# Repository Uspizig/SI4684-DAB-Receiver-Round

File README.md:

# Note:
The version in the repository is an ongoing development. It could and will contain bugs. To make sure you use the latest fully tested firmware, check the releases!

# Hint:
#define USE_HSPI_PORT ... set this to active in eTFT Lib user_setup.h. otherwise it won't work

# SI4684 DAB receiver
Advanced DAB Tuner software for Skyworks SI4684 tuner with ESP32 board and a round color LCD or AMOLED\
This is a fork of the famous PE5PVB SI4684 Project, unfinished and right now still in devolpment.
Check a more developed project on the origin source: https://www.pe5pvb.nl/

# How does it look

Simulation

Real device

# How does it look working

These are pictures of the very first HW bringup

Base Screen:

DAB Slideshow

# Libraries
These are the libraries used for this project:
- https://github.com/Bodmer/TFT_eSPI
- https://github.com/uzi18/TFT_eSPI
- https://github.com/Bodmer/JPEGDecoder
- https://github.com/bitbank2/PNGdec

Use these settings in the TFT_eSPI library:
```
#define ILI9341_2_DRIVER     // Alternative ILI9341 driver, see https://github.com/Bodmer/TFT_eSPI/issues/1172
#define TFT_WIDTH  240 // ST7789 240 x 240 and 240 x 320
#define TFT_HEIGHT 320 // ST7789 240 x 320

#define TFT_CS    38  // Chip select PIN
#define TFT_MISO  39  // MISO PIN
#define TFT_DC    40  // Data Command control pin
#define TFT_RST   41  // Reset pin (could connect 
#define TFT_MOSI  42  // MOSI PIN
#define TFT_SCLK  10  // CLK PIN
#define SPI_FREQUENCY  27000000
#define SMOOTH_FONT
#define USE_HSPI_PORT ///// THIS IS IMPORTANT OTHERWISE NO CONTACT TO DAB TUNER
#define LOAD_GFXFF  // FreeFonts. Include access to the 48 Adafruit_GFX free fonts FF1 to FF48 and custom fonts
#define SPI_READ_FREQUENCY  20000000
#define SPI_TOUCH_FREQUENCY  2500000

```
# Buttons
A brief instruction for the buttons:
- Top encoder: Choose frequency or memory channel
- Bottom encoder: Choose service or set headphones volume
- (Not in use right now) Top button: Short press: Service information, Long press: Stand-by mode. 
- Middle button: Short press: Set mode, Long press: Open menu.
- Lower button: Toggle Slideshow view.
  
## Contributing
I'm open for a new ideas in our project. Feel free to share your thoughts in 

You are using my software and you found a difficulty? Please create new [issue] and describe your problem.

I also would like to invite you to join our Discord community where we share our ideas and help each other with some issues.\

Special thanks to all [contributors](https://github.com/PE5PVB/TEF-Nextion-Multiband/graphs/contributors). You are awesome! ❤️
## License
This program is free software; you can redistribute it and/or modify it under the terms of the GNU General Public License as published by the Free Software Foundation; either version 3 of the License, or (at your option) any later version.

This program is distributed in the hope that it will be useful, but WITHOUT ANY WARRANTY; without even the implied warranty of MERCHANTABILITY or FITNESS FOR A PARTICULAR PURPOSE. See the GNU General Public License for more details. 

## If you like this software. Contriubute to

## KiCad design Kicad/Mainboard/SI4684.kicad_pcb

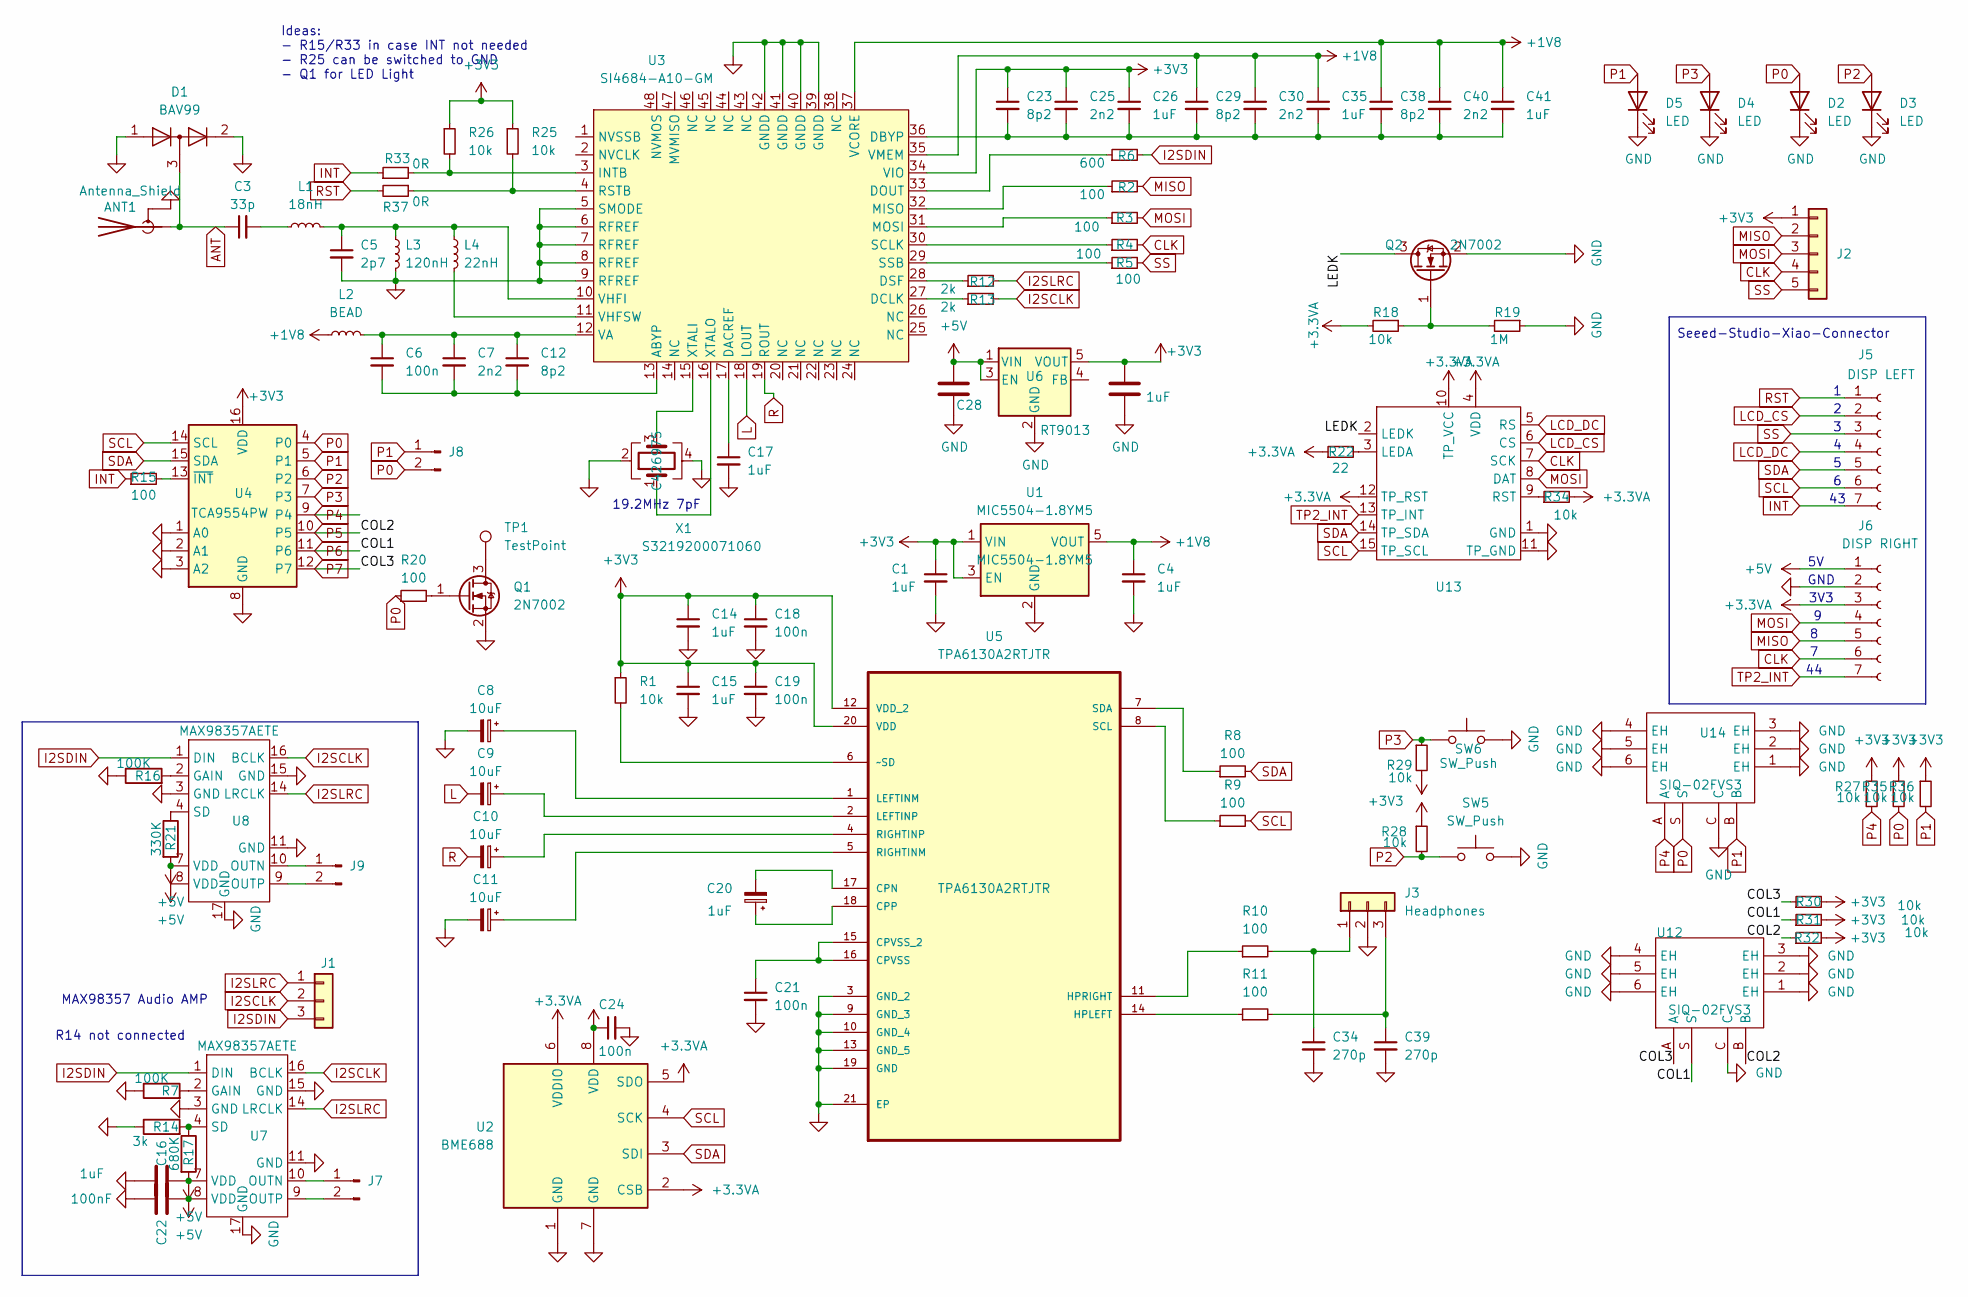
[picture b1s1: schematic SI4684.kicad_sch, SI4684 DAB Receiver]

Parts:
ANT1: Antenna_Shield; SMA_Samtec_SMA-J-P-H-ST-EM1_EdgeMount
C1, C4, C14, C15, C16, C17, C20, C26, C35, C41: 1uF; C_0603_1608Metric
C3: 33p; C_0603_1608Metric
C5: 2p7; C_0603_1608Metric_Pad1.08x0.95mm_HandSolder
C6, C18, C19, C21, C24: 100n; C_0603_1608Metric
C7, C25, C30, C40: 2n2; C_0603_1608Metric
C8, C9, C10, C11: 10uF; C_0805_2012Metric_Pad1.18x1.45mm_HandSolder
C12, C23, C29, C38: 8p2; C_0603_1608Metric
C22: 100nF; C_0603_1608Metric_Pad1.08x0.95mm_HandSolder
C28, C31: 1uF; C_0805_2012Metric_Pad1.18x1.45mm_HandSolder
C34, C39: 270p; C_0603_1608Metric
D1: BAV99; SOT-23W
D2, D4, D5: LED; LED_1210_3225Metric_Pad1.42x2.65mm_HandSolder
D3: LED; LED_1210_3225Metric
J1: Conn_01x03; PinHeader_1x03_P2.54mm_Vertical
J2: Conn_01x05; PinSocket_1x05_P2.54mm_Vertical_SMD_Pin1Left
J3: Headphones; JST_PH_B3B-PH-K_1x03_P2.00mm_Vertical
J5: DISP LEFT; PinHeader_1x07_P2.54mm_Vertical
J6: DISP RIGHT; PinHeader_1x07_P2.54mm_Vertical
J7, J9: Conn_01x02_Pin; PinHeader_1x02_P2.00mm_Vertical
J8: Conn_01x02_Pin; PinHeader_1x02_P2.54mm_Vertical
L1: 18nH; L_0603_1608Metric_Pad1.05x0.95mm_HandSolder
L2: BEAD; L_0603_1608Metric
L3: 120nH; L_0603_1608Metric_Pad1.05x0.95mm_HandSolder
L4: 22nH; L_0603_1608Metric_Pad1.05x0.95mm_HandSolder
Q1, Q2: 2N7002; SOT-23
R1, R18, R25, R26: 10k; R_0603_1608Metric
R2, R3, R4, R5, R8, R9, R10, R11, R15, R20: 100; R_0603_1608Metric
R6: 600; R_0603_1608Metric
R7, R16: 100K; R_0603_1608Metric_Pad0.98x0.95mm_HandSolder
R12, R13: 2k; R_0603_1608Metric
R14: 3k; R_0603_1608Metric_Pad0.98x0.95mm_HandSolder
R17: 680K; R_0603_1608Metric_Pad0.98x0.95mm_HandSolder
R19: 1M; R_0603_1608Metric
R21: 330K; R_0603_1608Metric_Pad0.98x0.95mm_HandSolder
R22: 22; R_0603_1608Metric
R27, R28, R29, R35, R36: 10k; R_0805_2012Metric_Pad1.20x1.40mm_HandSolder
R30, R31, R32, R34: 10k; R_0603_1608Metric_Pad0.98x0.95mm_HandSolder
R33, R37: 0R; R_0603_1608Metric
SW5, SW6: SW_Push; SW_SPST_CK_KMS2xxGP
TP1: TestPoint; TestPoint_Pad_D1.0mm
U1: MIC5504-1.8YM5; SOT-23-5
U2: BME688; Bosch_LGA-8_3x3mm_P0.8mm_ClockwisePinNumbering
U3: SI4684-A10-GM; QFN-48-1EP_7x7mm_P0.5mm_EP5.3x5.3mm
U4: TCA9554PW; TSSOP-16_4.4x5mm_P0.65mm
U5: TPA6130A2RTJTR; QFN-20-1EP_4x4mm_P0.5mm_EP2.7x2.7mm; MPN TPA6130A2RTJTR
U6: RT9013; SOT-23-5
U7, U8: MAX98357AETE; TQFN-16_L3.0-W3.0-P0.50-BL-EP1.5
U12, U14: SIQ-02FVS3; SW-SMD_SIQ-02FVS3_1; Manufacturer Part SIQ-02FVS3; LCSC Part Name 拨轮滚轮旋转编码器开关
U13: GC9A01_Touch_IPS_display_reversed_16pin
X1: S3219200071060; Crystal_SMD_3225-4Pin_3.2x2.5mm

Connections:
+1V8: C4.1, C29.1, C30.1, C35.1, C38.1, C40.1, C41.1, L2.1, U1.5 (VOUT), U3.35 (VMEM), U3.37 (VCORE)
+3.3VA: C24.1, J6.3, R18.2, R22.1, R34.2, U2.2 (CSB), U2.5 (SDO), U2.6 (VDDIO), U2.8 (VDD), U13.4 (VDD), U13.10 (TP_VCC), U13.12 (TP_RST)
+3V3: C1.1, C14.1, C15.1, C18.1, C19.1, C23.1, C25.1, C26.1, C31.2, J2.1, R1.1, R25.1, R26.1, R27.1, R28.1, R29.2, R30.2, R31.2, R32.2, R35.1, R36.1, U1.1 (VIN), U1.3 (EN), U3.34 (VIO), U4.16 (VDD), U5.12 (VDD_2), U5.20 (VDD), U6.5 (VOUT)
+5V: C16.1, C22.1, C28.2, J6.1, R17.2, R21.2, U6.1 (VIN), U6.3 (EN), U7.7 (VDD), U7.8 (VDD), U8.7 (VDD), U8.8 (VDD)
/LEDK: Q2.3 (D), U13.2 (LEDK)
ANT: ANT1.1 (A), C3.1, D1.3 (K); also elsewhere on the board
CLK: J2.4, J6.6, R4.2, U13.7 (SCK)
GND: ANT1.2 (Shield), C1.2, C4.2, C5.2, C8.2, C11.2, C14.2, C15.2, C16.2, C17.2, C18.2, C19.2, C21.2, C22.2, C24.2, C28.1, C31.1, C34.2, C39.2, D1.1 (K), D1.2 (A), D2.1 (K), D3.1 (K), D4.1 (K), D5.1 (K), J3.2, J6.2, L3.2, Q1.2 (S), Q2.2 (S), R7.1, R14.1, R16.1, R19.1, SW5.2, SW6.2, U1.2 (GND), U2.1 (GND), U2.7 (GND), U3.5 (SMODE), U3.6 (RFREF), U3.7 (RFREF), U3.8 (RFREF), U3.9 (RFREF), U3.39 (GNDD), U3.40 (GNDD), U3.41 (GNDD), U3.42 (GNDD), U3.49 (GND), U4.1 (A0), U4.2 (A1), U4.3 (A2), U4.8 (GND), U5.3 (GND_2), U5.9 (GND_3), U5.10 (GND_4), U5.13 (GND_5), U5.19 (GND), U5.21 (EP), U6.2 (GND), U7.3 (GND), U7.11 (GND), U7.15 (GND), U7.17 (GND), U8.3 (GND), U8.11 (GND), U8.15 (GND), U8.17 (GND), U12.1 (EH), U12.2 (EH), U12.3 (EH), U12.4 (EH), U12.5 (EH), U12.6 (EH), U12.C, U13.1 (GND), U13.11 (TP_GND), U14.1 (EH), U14.2 (EH), U14.3 (EH), U14.4 (EH), U14.5 (EH), U14.6 (EH), U14.C, X1.2, X1.4; also elsewhere on the board
I2SCLK: J1.2, R13.2, U7.16 (BCLK), U8.16 (BCLK)
I2SDIN: J1.3, R6.2, U7.1 (DIN), U8.1 (DIN)
I2SLRC: J1.1, R12.2, U7.14 (LRCLK), U8.14 (LRCLK)
INT: J5.7, R15.1, R33.1
L: C9.2, U3.18 (LOUT)
LCD_CS: J5.2, U13.6 (CS)
LCD_DC: J5.4, U13.5 (RS)
MISO: J2.2, J6.5, R2.2
MOSI: J2.3, J6.4, R3.2, U13.8 (DAT)
unnamed: C3.2, L1.1
unnamed: C34.1, J3.1, R10.2
unnamed: C39.1, J3.3, R11.2
unnamed: J7.1, U7.10 (OUTN)
unnamed: J7.2, U7.9 (OUTP)
unnamed: J9.1, U8.10 (OUTN)
unnamed: J9.2, U8.9 (OUTP)
unnamed: Q1.3 (D), TP1.1
unnamed: Q1.1 (G), R20.2
unnamed: Q2.1 (G), R18.1, R19.2
unnamed: C6.2, C7.2, C12.2, U3.13 (ABYP)
unnamed: C17.1, U3.17 (DACREF)
unnamed: C23.2, C25.2, C26.2, C29.2, C30.2, C35.2, C38.2, C40.2, C41.2, U3.36 (DBYP)
unnamed: R13.1, U3.27 (DCLK)
unnamed: R6.1, U3.33 (DOUT)
unnamed: R12.1, U3.28 (DSF)
unnamed: R26.2, R33.2, U3.3 (INTB)
unnamed: R2.1, U3.32 (MISO)
unnamed: R3.1, U3.31 (MOSI)
unnamed: R25.2, R37.1, U3.4 (RSTB)
unnamed: R4.1, U3.30 (SCLK)
unnamed: R5.1, U3.29 (SSB)
unnamed: C6.1, C7.1, C12.1, L2.2, U3.12 (VA)
unnamed: C5.1, L1.2, L3.1, L4.1, U3.10 (VHFI)
unnamed: L4.2, U3.11 (VHFSW)
unnamed: U3.15 (XTALI), X1.3
unnamed: U3.16 (XTALO), X1.1
unnamed: R15.2, U4.13 (~INT)
unnamed: C20.2, U5.17 (CPN)
unnamed: C20.1, U5.18 (CPP)
unnamed: C21.1, U5.15 (CPVSS_2), U5.16 (CPVSS)
unnamed: R11.1, U5.14 (HPLEFT)
unnamed: R10.1, U5.11 (HPRIGHT)
unnamed: C8.1, U5.1 (LEFTINM)
unnamed: C9.1, U5.2 (LEFTINP)
unnamed: C11.1, U5.5 (RIGHTINM)
unnamed: C10.1, U5.4 (RIGHTINP)
unnamed: R9.1, U5.8 (SCL)
unnamed: R8.1, U5.7 (SDA)
unnamed: R1.2, U5.6 (~SD)
unnamed: R7.2, U7.2 (GAIN)
unnamed: R14.2, R17.1, U7.4 (SD)
unnamed: R16.2, U8.2 (GAIN)
unnamed: R21.1, U8.4 (SD)
unnamed: R22.2, U13.3 (LEDA)
unnamed: R34.1, U13.9 (RST)
P0: D2.2 (A), J8.2, R20.1, R35.2, U4.4 (P0), U14.S
P1: D5.2 (A), J8.1, R36.2, U4.5 (P1), U14.B
P2: D3.2 (A), R28.2, SW5.1, U4.6 (P2)
P3: D4.2 (A), R29.1, SW6.1, U4.7 (P3)
P4: R27.2, U4.9 (P4), U14.A
P5: R32.1, U4.10 (P5), U12.B
P6: R31.1, U4.11 (P6), U12.S
P7: R30.1, U4.12 (P7), U12.A
R: C10.2, U3.19 (ROUT)
RST: J5.1, R37.2
SCL: J5.6, R9.2, U2.4 (SCK), U4.14 (SCL), U13.15 (TP_SCL)
SDA: J5.5, R8.2, U2.3 (SDI), U4.15 (SDA), U13.14 (TP_SDA)
SS: J2.5, J5.3, R5.2
TP2_INT: J6.7, U13.13 (TP_INT)

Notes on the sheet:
R14 not connected
MAX98357 Audio AMP
3V3
Seeed-Studio-Xiao-Connector
Ideas: - R15/R33 in case INT not needed - R25 can be switched to GND - Q1 for LED Light
19.2MHz 7pF
GND

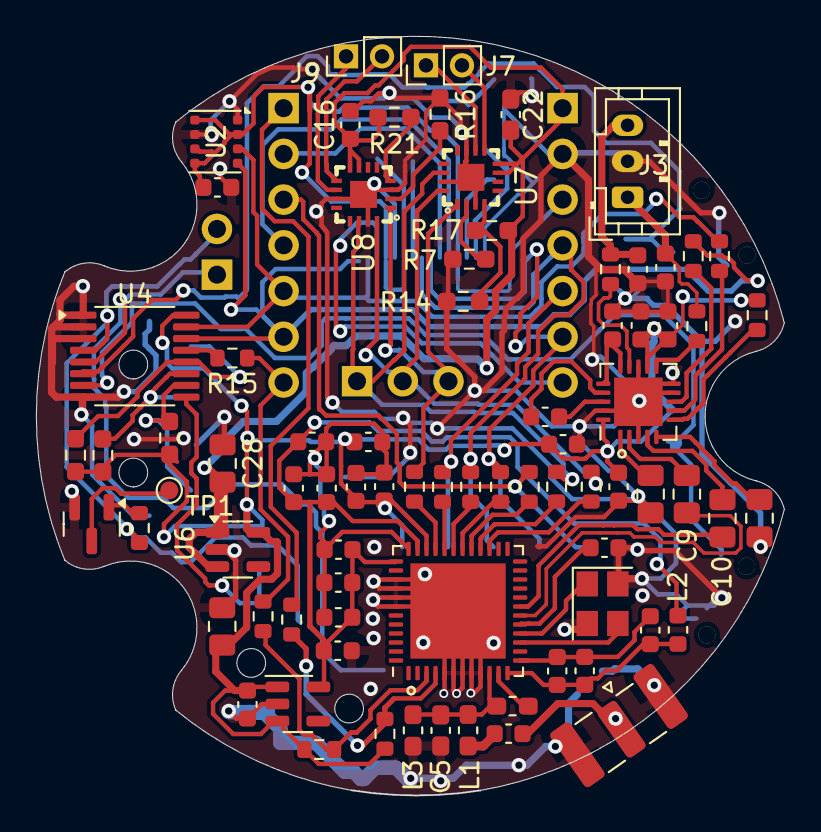
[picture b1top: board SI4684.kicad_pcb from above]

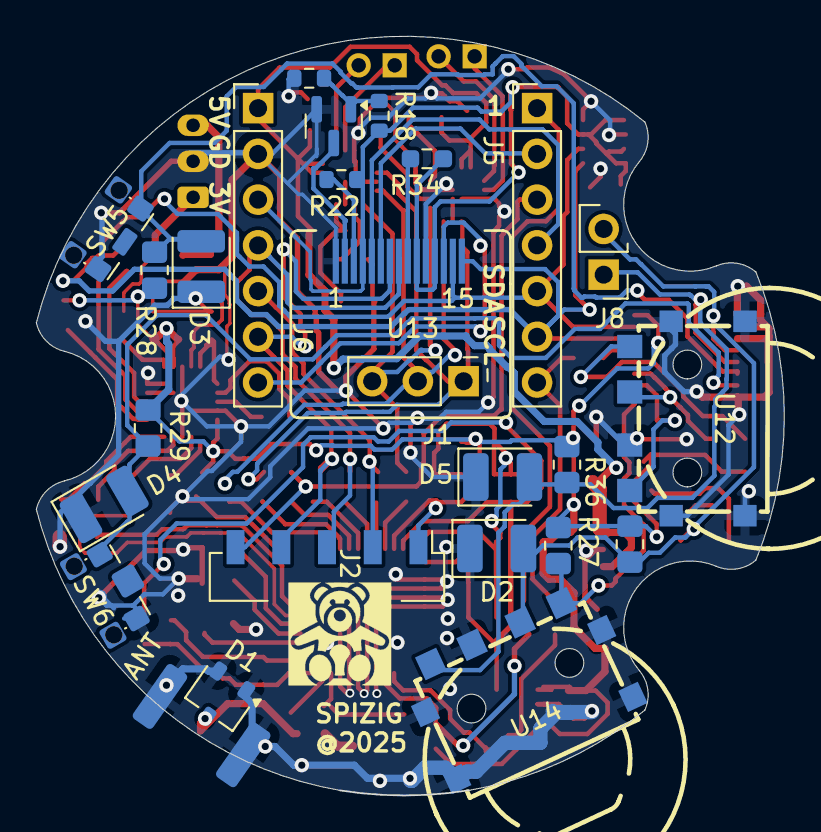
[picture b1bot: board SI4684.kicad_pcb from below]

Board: 2 copper layers, 41.6 x 42.2 mm, 105 parts (26 on the bottom side), 77 nets.

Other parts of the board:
ANT: Antenna_Shield; SMA_Samtec_SMA-J-P-H-ST-EM1_EdgeMount
H2: MountingHole; baerklein

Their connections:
ANT: ANT.1 (A); also elsewhere on the board
GND: ANT.2 (Shield); also elsewhere on the board

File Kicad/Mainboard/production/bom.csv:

Designator,Footprint,Quantity,Value,LCSC Part #
ANT,SMA_Samtec_SMA-J-P-H-ST-EM1_EdgeMount,1,Antenna_Shield,
"C1, C14, C15, C16, C17, C20, C26, C35, C4, C41",0603,10,1uF,
"C10, C11, C8, C9",0805,4,10uF,
"C12, C23, C29, C38",0603,4,8p2,
"C18, C19, C21, C24, C6",0603,5,100n,
C22,0603,1,100nF,
"C25, C30, C40, C7",0603,4,2n2,
"C28, C31",0805,2,1uF,
C3,0603,1,33p,
"C34, C39",0603,2,270p,
C5,0603,1,2p7,
D1,SOT-23W,1,BAV99,
"D2, D3, D4, D5",1210,4,LED,
J1,PinHeader_1x03_P2.54mm_Vertical,1,Conn_01x03,
J2,PinSocket_1x05_P2.54mm_Vertical_SMD_Pin1Left,1,Conn_01x05,
J3,JST_PH_B3B-PH-K_1x03_P2.00mm_Vertical,1,Headphones,
J5,PinHeader_1x07_P2.54mm_Vertical,1,DISP LEFT,
J6,PinHeader_1x07_P2.54mm_Vertical,1,DISP RIGHT,
"J7, J9",PinHeader_1x02_P2.00mm_Vertical,2,Conn_01x02_Pin,
J8,PinHeader_1x02_P2.54mm_Vertical,1,Conn_01x02_Pin,
L1,0603,1,18nH,
L2,0603,1,BEAD,
L3,0603,1,120nH,
L4,0603,1,22nH,
"Q1, Q2",SOT-23,2,2N7002,
"R1, R18, R25, R26, R30, R31, R32, R34",0603,8,10k,
"R10, R11, R15, R2, R20, R3, R4, R5, R8, R9",0603,10,100,
"R12, R13",0603,2,2k,
R14,0603,1,3k,
"R16, R7",0603,2,100K,
R17,0603,1,680K,
R19,0603,1,1M,
R21,0603,1,330K,
R22,0603,1,22,
"R27, R28, R29, R35, R36",0805,5,10k,
"R33, R37",0603,2,0R,
R6,0603,1,600,
"SW5, SW6",SW_SPST_CK_KMS2xxGP,2,SW_Push,
TP1,TestPoint_Pad_D1.0mm,1,TestPoint,
U1,SOT-23-5,1,MIC5504-1.8YM5,
"U12, U14",SW-SMD_SIQ-02FVS3_1,2,SIQ-02FVS3,
U13,GC9A01_Touch_IPS_display_reversed_16pin,1,~,
U2,Bosch_LGA-8_3x3mm_P0.8mm_ClockwisePinNumbering,1,BME688,
U3,QFN-48-1EP_7x7mm_P0.5mm_EP5.3x5.3mm,1,SI4684-A10-GM,
U4,TSSOP-16_4.4x5mm_P0.65mm,1,TCA9554PW,
U5,QFN-20-1EP_4x4mm_P0.5mm_EP2.7x2.7mm,1,TPA6130A2RTJTR,  TPA6130A2RTJTR
U6,SOT-23-5,1,RT9013,
"U7, U8",TQFN-16_L3.0-W3.0-P0.50-BL-EP1.5,2,MAX98357AETE,
X1,Crystal_SMD_3225-4Pin_3.2x2.5mm,1,S3219200071060,

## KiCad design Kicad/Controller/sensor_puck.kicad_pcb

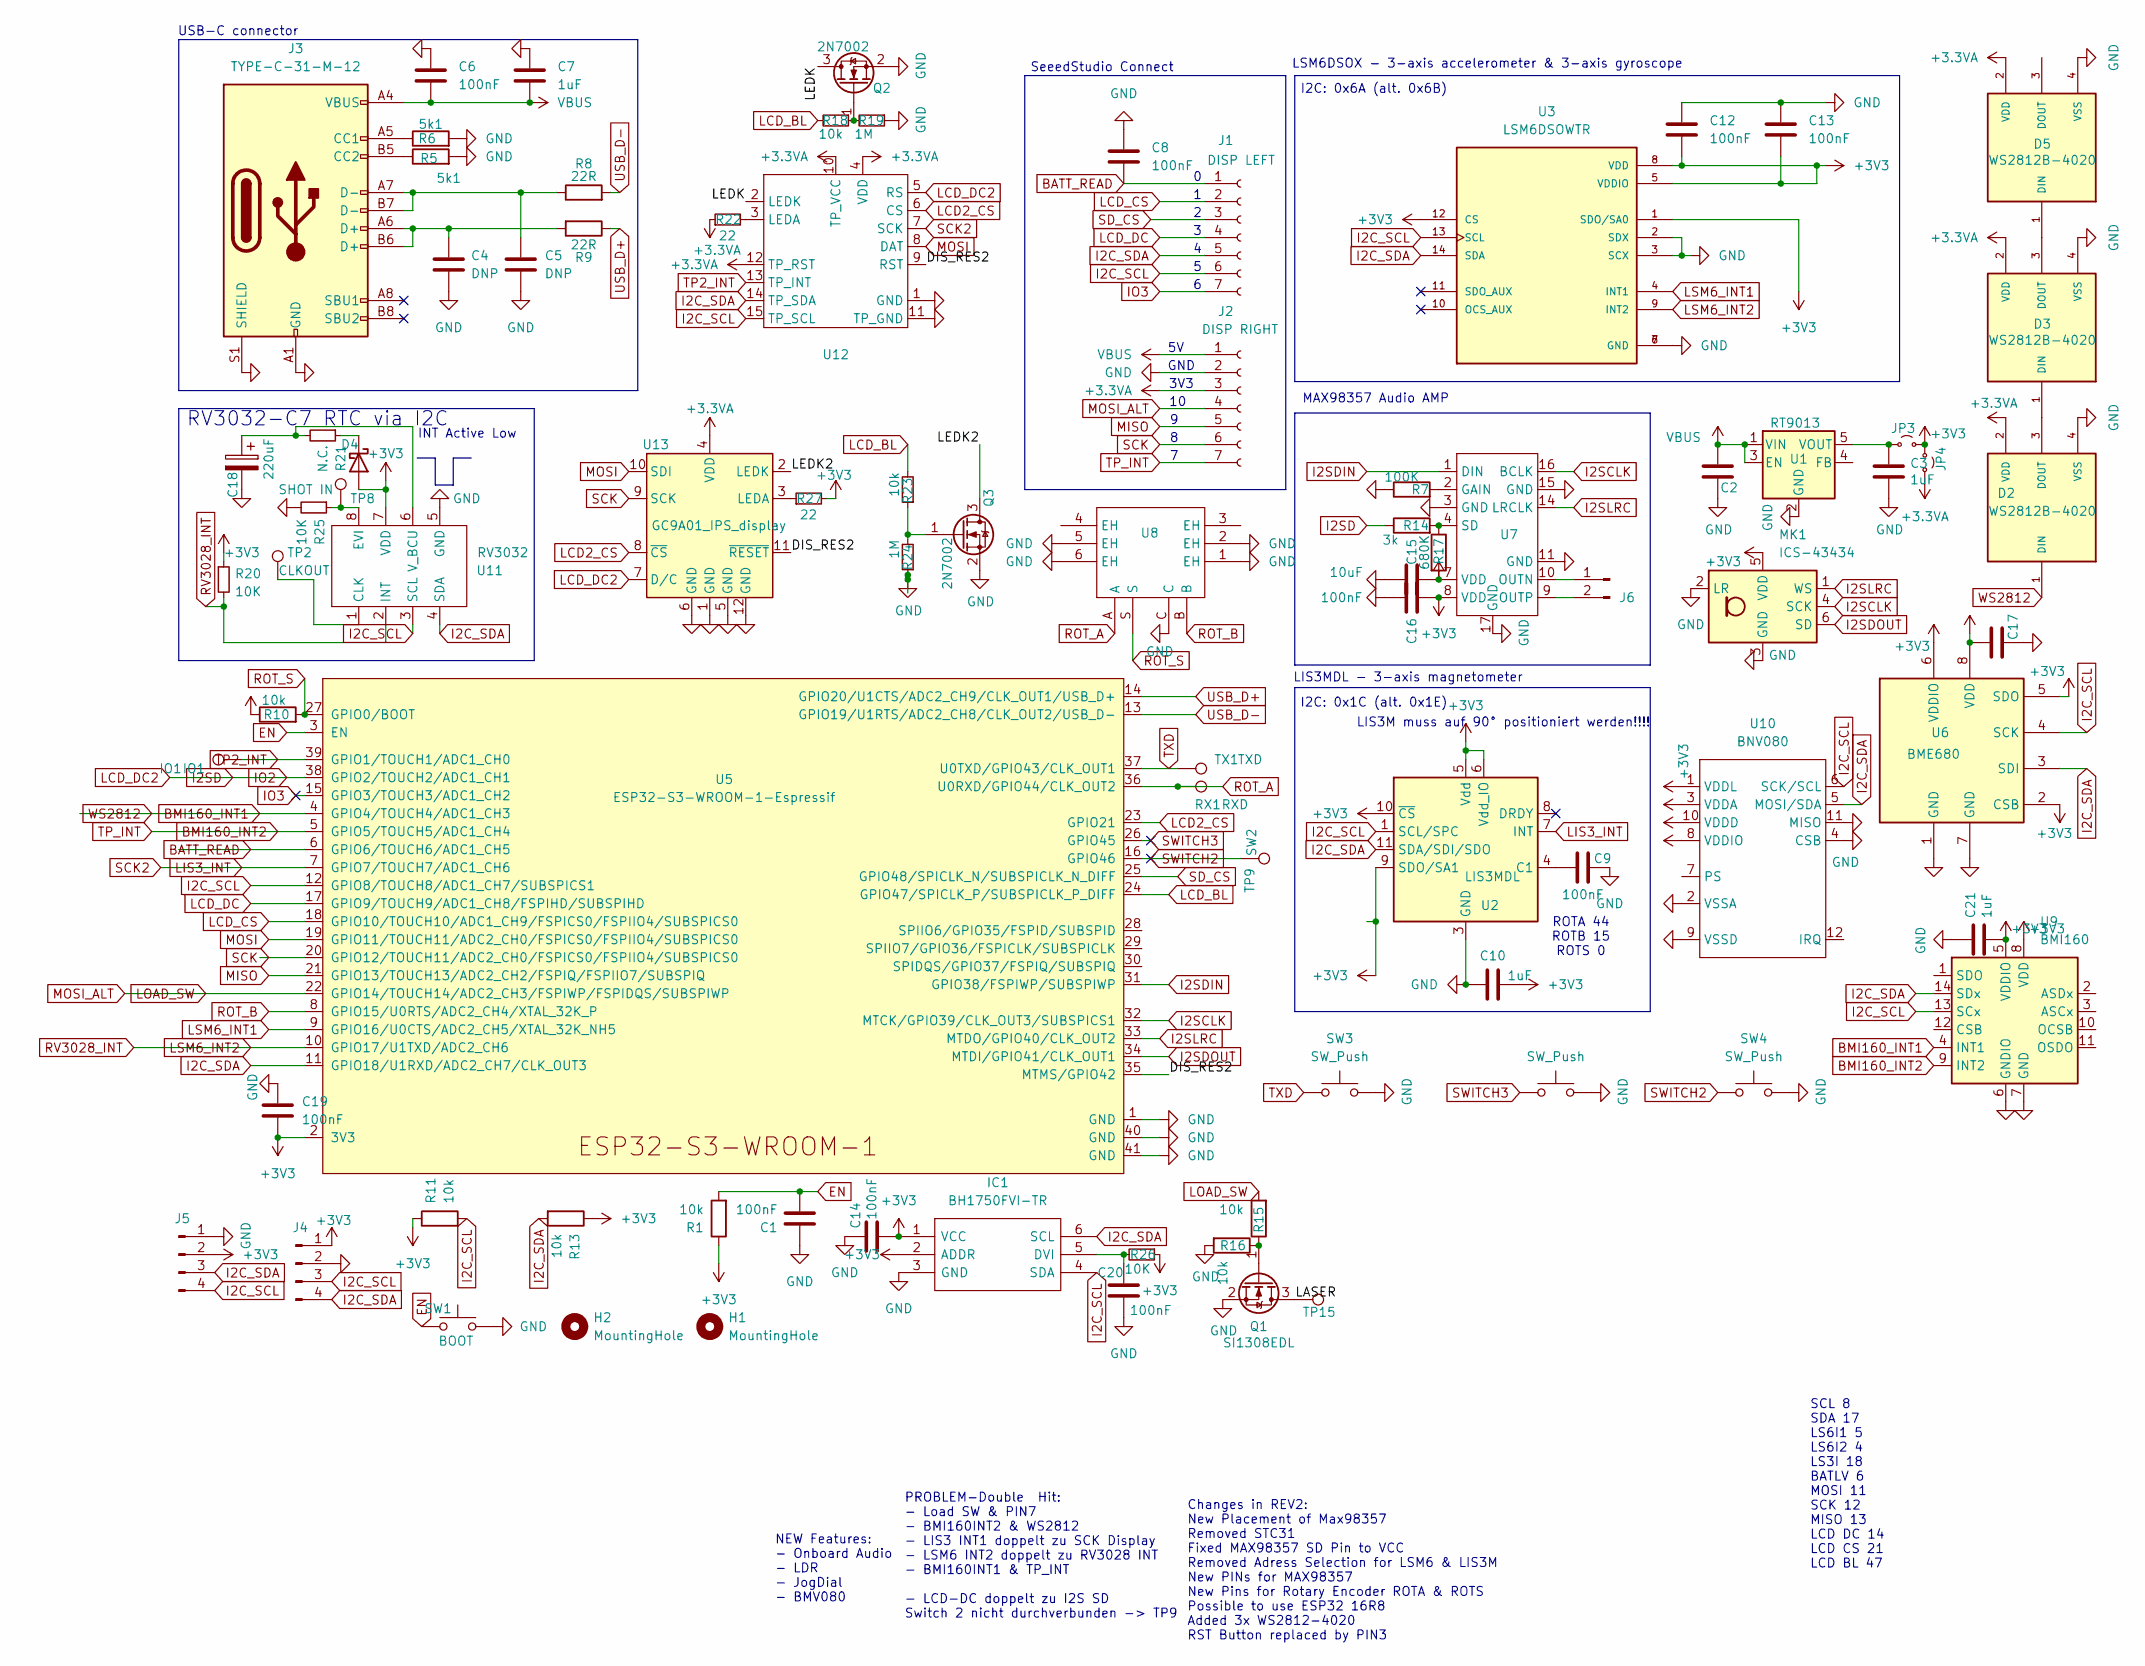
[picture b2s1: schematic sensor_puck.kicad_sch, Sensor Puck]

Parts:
C1: 100nF; C_1206_3216Metric_Pad1.33x1.80mm_HandSolder
C2, C3, C17, C21: 1uF; C_0805_2012Metric_Pad1.18x1.45mm_HandSolder
C4, C5: DNP; C_0805_2012Metric
C6, C8, C9, C12, C13, C14, C19: 100nF; C_0805_2012Metric
C7, C10: 1uF; C_0805_2012Metric
C15: 10uF; C_0805_2012Metric_Pad1.18x1.45mm_HandSolder
C16: 100nF; C_0805_2012Metric_Pad1.18x1.45mm_HandSolder
C18: 220uF; CP_EIA-3528-21_Kemet-B
C20: 100nF; C_0603_1608Metric
D2, D3, D5: WS2812B-4020; LED_WS2812B-4020; PARTREV V1.2
D4: MBR0530; D_SOD-323F
H1, H2: MountingHole; baerklein
IC1: BH1750FVI-TR; WSOF6; Mouser Part Number 755-BH1750FVI-TR
IO1: IO1; TestPoint_Pad_1.0x1.0mm
J1: DISP LEFT; PinHeader_1x07_P2.54mm_Vertical
J2: DISP RIGHT; PinHeader_1x07_P2.54mm_Vertical
J3: TYPE-C-31-M-12; USB-C_SMD-TYPE-C-31-M-12
J4: Conn_01x04_Pin; PinHeader_1x04_P2.54mm_Vertical_SMD_Pin1Left
J5: Conn_01x04_Pin; JST_SH_SM04B-SRSS-TB_1x04-1MP_P1.00mm_Horizontal
J6: Conn_01x02_Pin; PinHeader_1x02_P2.00mm_Vertical
JP3, JP4: Jumper_2_Small_Open; SolderJumper-2_P1.3mm_Open_RoundedPad1.0x1.5mm
MK1: ICS-43434; InvenSense_ICS-43434-6_3.5x2.65mm
Q1: SI1308EDL; SOT-323_SC-70
Q2, Q3: 2N7002; SOT-23
R1: 10k; R_0805_2012Metric_Pad1.20x1.40mm_HandSolder
R5, R6: 5k1; R_0805_2012Metric
R7: 100K; R_0805_2012Metric_Pad1.20x1.40mm_HandSolder
R8, R9: 22R; R_0805_2012Metric
R10, R11, R13: 10k; R_0805_2012Metric
R14: 3k; R_0805_2012Metric_Pad1.20x1.40mm_HandSolder
R15, R16: 10k; R_0603_1608Metric_Pad0.98x0.95mm_HandSolder
R17: 680K; R_0805_2012Metric_Pad1.20x1.40mm_HandSolder
R18, R23: 10k; R_0603_1608Metric
R19, R24: 1M; R_0603_1608Metric
R20, R25, R26: 10K; R_0603_1608Metric_Pad0.98x0.95mm_HandSolder; LCSC C17414
R21: N.C.; C_0603_1608Metric
R22, R27: 22; R_0603_1608Metric
RX1: RXD; TestPoint_Pad_1.0x1.0mm
SW1: BOOT; SW_PUSH_6mm
SW3, SW4, SW6: SW_Push; SW_SPST_CK_KMS2xxGP
TP2: CLKOUT; TestPoint_Pad_D1.0mm
TP8: SHOT IN; TestPoint_Pad_D1.0mm
TP9: SW2; TestPoint_Pad_D1.0mm
TP15: TestPoint; TestPoint_Pad_D1.0mm
TX1: TXD; TestPoint_Pad_1.0x1.0mm
U1: RT9013; SOT-23-5
U2: LIS3MDL; LGA-12_2x2mm_P0.5mm
U3: LSM6DSOWTR; LGA-14_3x2.5mm_P0.5mm_LayoutBorder3x4y; PARTREV 3.0
U5: ESP32-S3-WROOM-1-Espressif; ESP32-S3-WROOM-1
U6: BME680; Bosch_LGA-8_3x3mm_P0.8mm_ClockwisePinNumbering
U7: TQFN-16_L3.0-W3.0-P0.50-BL-EP1.5
U8: SW-SMD_SIQ-02FVS3_1; Manufacturer Part SIQ-02FVS3; LCSC Part Name 拨轮滚轮旋转编码器开关
U9: BMI160; Bosch_LGA-14_3x2.5mm_P0.5mm
U10: BNV080; 046844713002846
U11: RV3032; MicroCrystal_C7_SON-8_1.5x3.2mm_P0.9mm
U12: GC9A01_Touch_IPS_display_reversed_16pin
U13: GC9A01_IPS_display; GC9A01_IPS_display_reversed

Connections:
+3.3VA: D2.2 (VDD), D3.2 (VDD), D5.2 (VDD), J2.3, JP4.2 (B), R22.1, U12.4 (VDD), U12.10 (TP_VCC), U12.12 (TP_RST), U13.4 (VDD)
+3V3: C10.2, C12.2, C13.2, C14.2, C15.1, C16.1, C17.2, C19.2, C21.1, D4.2 (A), IC1.1 (VCC), IC1.2 (ADDR), J4.1, J5.2, JP3.2 (B), JP4.1 (A), MK1.5 (VDD), R1.1, R10.1, R11.1, R13.1, R17.2, R20.1, R26.1, R27.2, U2.5 (Vdd), U2.6 (Vdd_IO), U2.9 (SDO/SA1), U2.10 (~CS), U3.1 (SDO/SA0), U3.5 (VDDIO), U3.8 (VDD), U3.12 (CS), U5.2 (3V3), U6.2 (CSB), U6.5 (SDO), U6.6 (VDDIO), U6.8 (VDD), U7.7 (VDD), U7.8 (VDD), U9.5 (VDDIO), U9.8 (VDD), U10.1 (VDDL), U10.3 (VDDA), U10.8 (VDDIO), U10.10 (VDDD), U11.7 (VDD)
/DIS_RES2: U5.35 (MTMS/GPIO42), U12.9 (RST), U13.11 (~RESET)
/LASER: Q1.3 (D), TP15.1
/LEDK: Q2.3 (D), U12.2 (LEDK)
/LEDK2: Q3.3 (D), U13.2 (LEDK)
BATT_READ: C8.1, J1.1, U5.6 (GPIO6/TOUCH6/ADC1_CH5)
BMI160_INT1: D2.1 (DIN), U5.4 (GPIO4/TOUCH4/ADC1_CH3), U9.4 (INT1)
BMI160_INT2: J2.7, U5.5 (GPIO5/TOUCH5/ADC1_CH4), U9.9 (INT2)
EN: C1.2, R1.2, SW1.1, U5.3 (EN)
GND: C1.1, C2.1, C3.1, C4.2, C5.2, C6.1, C7.1, C8.2, C9.2, C10.1, C12.1, C13.1, C14.1, C15.2, C16.2, C17.1, C18.2, C19.1, C20.2, C21.2, D2.4 (VSS), D3.4 (VSS), D5.4 (VSS), IC1.3 (GND), J2.2, J3.A1 (GND), J3.A12 (GND), J3.B1 (GND), J3.B12 (GND), J3.S1 (SHIELD), J4.2, J5.1, MK1.2 (LR), MK1.3 (GND), Q1.2 (S), Q2.2 (S), Q3.2 (S), R5.2, R6.2, R7.1, R16.2, R19.1, R24.1, R25.2, SW1.2, SW3.2, SW4.2, SW6.2, U1.2 (GND), U2.2 (GND), U2.3 (GND), U2.12 (GND), U3.2 (SDX), U3.3 (SCX), U3.6 (GND), U3.7 (GND), U5.1 (GND), U5.40 (GND), U5.41 (GND), U6.1 (GND), U6.7 (GND), U7.3 (GND), U7.11 (GND), U7.15 (GND), U7.17 (GND), U8.1 (EH), U8.2 (EH), U8.5 (EH), U8.6 (EH), U8.C, U9.6 (GNDIO), U9.7 (GND), U10.2 (VSSA), U10.4 (CSB), U10.9 (VSSD), U10.11 (MISO), U11.5 (GND), U12.1 (GND), U12.11 (TP_GND), U13.1 (GND), U13.5 (GND), U13.6 (GND), U13.12 (GND)
I2C_SCL: IC1.4 (SDA), J1.6, J4.3, J5.4, R11.2, U2.1 (SCL/SPC), U3.13 (SCL), U5.12 (GPIO8/TOUCH8/ADC1_CH7/SUBSPICS1), U6.4 (SCK), U9.13 (SCx), U10.6 (SCK/SCL), U11.3 (SCL), U12.15 (TP_SCL)
I2C_SDA: IC1.6 (SCL), J1.5, J4.4, J5.3, R13.2, U2.11 (SDA/SDI/SDO), U3.14 (SDA), U5.11 (GPIO18/U1RXD/ADC2_CH7/CLK_OUT3), U6.3 (SDI), U9.14 (SDx), U10.5 (MOSI/SDA), U11.4 (SDA), U12.14 (TP_SDA)
I2SCLK: MK1.4 (SCK), U5.32 (MTCK/GPIO39/CLK_OUT3/SUBSPICS1), U7.16 (BCLK)
I2SD: R14.1, U5.38 (GPIO2/TOUCH2/ADC1_CH1), U12.5 (RS), U13.7 (D/C)
I2SDIN: U5.31 (GPIO38/FSPIWP/SUBSPIWP), U7.1 (DIN)
I2SDOUT: MK1.6 (SD), U5.34 (MTDI/GPIO41/CLK_OUT1)
I2SLRC: MK1.1 (WS), U5.33 (MTDO/GPIO40/CLK_OUT2), U7.14 (LRCLK)
IO3: J1.7, U5.15 (GPIO3/TOUCH3/ADC1_CH2)
LCD2_CS: U5.23 (GPIO21), U12.6 (CS), U13.8 (~CS)
LCD_BL: R18.2, R23.2, U5.24 (GPIO47/SPICLK_P/SUBSPICLK_P_DIFF)
LCD_CS: J1.2, U5.18 (GPIO10/TOUCH10/ADC1_CH9/FSPICS0/FSPIIO4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)
LCD_DC: J1.4, U5.17 (GPIO9/TOUCH9/ADC1_CH8/FSPIHD/SUBSPIHD)
LIS3_INT: U2.7 (INT), U5.7 (GPIO7/TOUCH7/ADC1_CH6), U12.7 (SCK)
LOAD_SW: J2.4, R15.2, U5.22 (GPIO14/TOUCH14/ADC2_CH3/FSPIWP/FSPIDQS/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)
LSM6_INT1: U3.4 (INT1), U5.9 (GPIO16/U0CTS/ADC2_CH5/XTAL_32K_NH5)
LSM6_INT2: R20.2, U3.9 (INT2), U5.10 (GPIO17/U1TXD/ADC2_CH6), U11.2 (INT)
MISO: J2.5, U5.21 (GPIO13/TOUCH13/ADC2_CH2/FSPIQ/FSPIIO7/S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)
MOSI: U5.19 (GPIO11/TOUCH11/ADC2_CH0/FSPICS0/FSPIIO4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), U12.8 (DAT), U13.10 (SDI)
unnamed: C4.1, J3.A6 (D+), J3.B6 (D+), R9.2
unnamed: C5.1, J3.A7 (D-), J3.B7 (D-), R8.1
unnamed: D2.3 (DOUT), D3.1 (DIN)
unnamed: D3.3 (DOUT), D5.1 (DIN)
unnamed: D4.1 (K), R21.1
unnamed: C20.1, IC1.5 (DVI), R26.2
unnamed: J3.A5 (CC1), R6.1
unnamed: J3.B5 (CC2), R5.1
unnamed: J6.1, U7.10 (OUTN)
unnamed: J6.2, U7.9 (OUTP)
unnamed: C3.2, JP3.1 (A), U1.5 (VOUT)
unnamed: Q1.1 (G), R15.1, R16.1
unnamed: Q2.1 (G), R18.1, R19.2
unnamed: Q3.1 (G), R23.1, R24.2
unnamed: C9.1, U2.4 (C1)
unnamed: R7.2, U7.2 (GAIN)
unnamed: R14.2, R17.1, U7.4 (SD)
unnamed: TP2.1, U11.1 (CLK)
unnamed: R25.1, TP8.1, U11.8 (EVI)
unnamed: C18.1, R21.2, U11.6 (V_BCU)
unnamed: R22.2, U12.3 (LEDA)
unnamed: R27.1, U13.3 (LEDA)
ROT_A: RX1.1, U5.36 (U0RXD/GPIO44/CLK_OUT2), U8.A
ROT_B: U5.8 (GPIO15/U0RTS/ADC2_CH4/XTAL_32K_P), U8.B
ROT_S: R10.2, U5.27 (GPIO0/BOOT), U8.S
SCK: J2.6, U5.20 (GPIO12/TOUCH11/ADC2_CH0/FSPICS0/FSPIIO4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), U13.9 (SCK)
SD_CS: J1.3, U5.25 (GPIO48/SPICLK_N/SUBSPICLK_N_DIFF)
SWITCH3: SW6.1, U5.26 (GPIO45)
TP2_INT: IO1.1, U5.39 (GPIO1/TOUCH1/ADC1_CH0), U12.13 (TP_INT)
TXD: SW3.1, TX1.1, U5.37 (U0TXD/GPIO43/CLK_OUT1)
USB_D+: R9.1, U5.14 (GPIO20/U1CTS/ADC2_CH9/CLK_OUT1/USB_D+)
USB_D-: R8.2, U5.13 (GPIO19/U1RTS/ADC2_CH8/CLK_OUT2/USB_D-)
VBUS: C2.2, C6.2, C7.2, J2.1, J3.A4 (VBUS), J3.A9 (VBUS), J3.B4 (VBUS), J3.B9 (VBUS), U1.1 (VIN), U1.3 (EN)

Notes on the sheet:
USB-C connector
PROBLEM-Double Hit: - Load SW & PIN7 - BMI160INT2 & WS2812 - LIS3 INT1 doppelt zu SCK Display - LSM6 INT2 doppelt zu RV3028 INT - BMI160INT1 & TP_INT - LCD-DC doppelt zu I2S SD Switch 2 nicht durchverbunden -> TP9
INT Active Low
LIS3M muss auf 90° positioniert werden!!!!
SeeedStudio Connect
SCL 8 SDA 17 LS6I1 5 LS6I2 4 LS3I 18 BATLV 6 MOSI 11 SCK 12 MISO 13 LCD DC 14 LCD CS 21 LCD BL 47
I2C: 0x1C (alt. 0x1E)
NEW Features: - Onboard Audio - LDR - JogDial - BMV080
Changes in REV2: New Placement of Max98357 Removed STC31 Fixed MAX98357 SD Pin to VCC Removed Adress Selection for LSM6 & LIS3M New PINs for MAX98357 New Pins for Rotary Encoder ROTA & ROTS Possible to use ESP32 16R8 Added 3x WS2812-4020 RST Button replaced by PIN3
I2C: 0x6A (alt. 0x6B)
LIS3MDL - 3-axis magnetometer
RV3032-C7 RTC via I2C
MAX98357 Audio AMP
GND
LSM6DSOX - 3-axis accelerometer & 3-axis gyroscope
ROTA 44 ROTB 15 ROTS 0
3V3

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
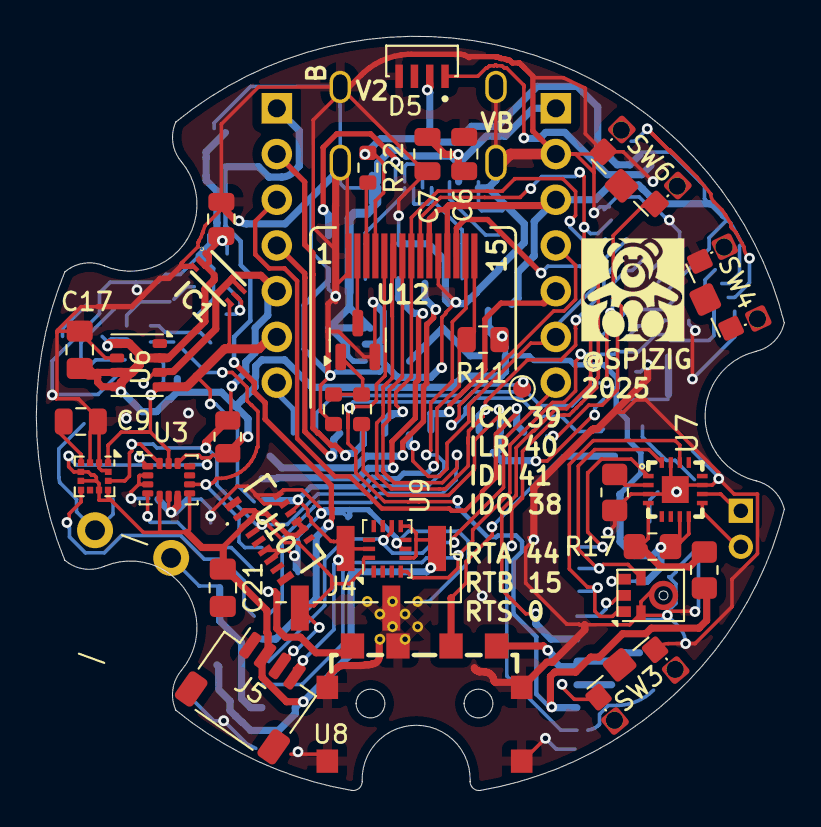
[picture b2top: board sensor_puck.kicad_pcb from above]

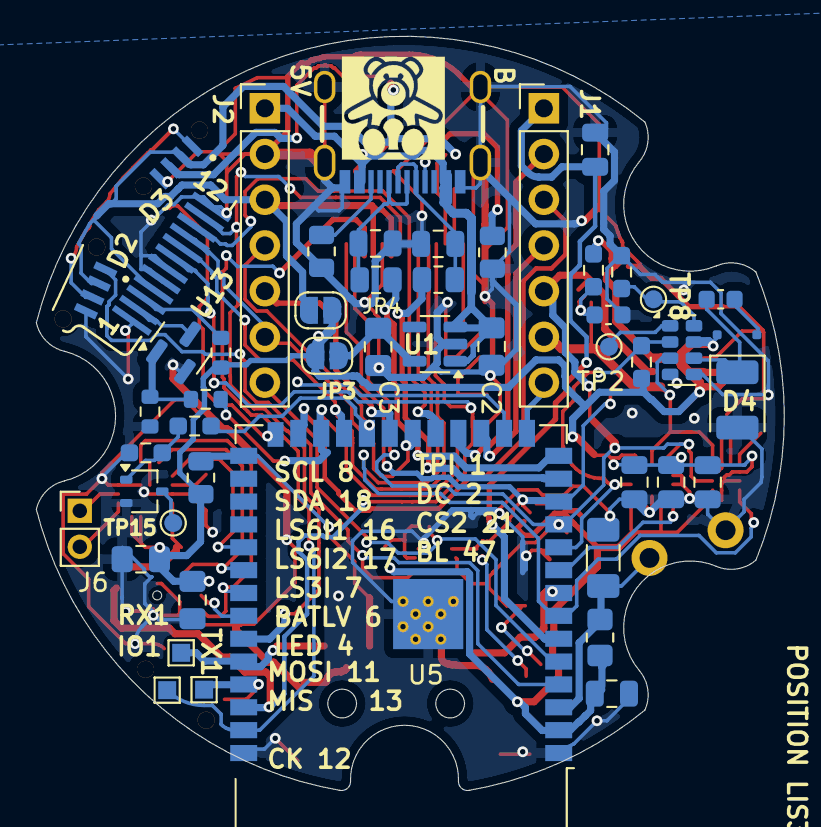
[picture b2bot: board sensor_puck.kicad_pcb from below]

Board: 2 copper layers, 41.6 x 41.9 mm, 85 parts (51 on the bottom side), 63 nets.

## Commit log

2025-06-04 Add files via upload
    work in progress. not finished
2025-06-04 Add files via upload
    fixed some layout issues. still work in progress
2025-06-05 Add files via upload
    added Display connector
2025-06-05 Update README.md
    added Round Display Lib Fork of TFT_eSPI from UZI18 for ST77916 Round Display
2025-06-10 Delete Kicad/Controller directory
    not needed any more
2025-06-10 Add files via upload
    - Added second Rotary encoder
    - Removed need for Motherboard
    - Removed Switch P4 (Slideshow Switch)
    - Did a lot of Rerouting
    - Performed some DRC Checks
    (still not final)... work in Progress
2025-08-13 Update SI4684-DAB-Receiver.ino
    changed littlefs access
2025-08-13 Add files via upload
    debugging
2025-08-13 Update README.md
    #define USE_HSPI_PORT
    in eTFT Lib is essential
2025-08-22 Add files via upload
    Beware... 2 parts missing 2.7pF and 2x 270pf
    and some for the backside
2025-08-22 Update README.md
    corrected some typos
2025-08-22 Delete Kicad/Controller directory
    not neeeded

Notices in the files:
README.md:
https://img.shields.io/badge/license%20-%20GNU_GPLv3-GPLv3?color=blue
